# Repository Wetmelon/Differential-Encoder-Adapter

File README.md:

# Differential Encoder Adapter

This project is dedicated to a simple adapter board designed to convert 5V line driver encoders to single-ended encoders for use with the ODrive 3.x servo driver.

[Order Boards Here](https://oshpark.com/shared_projects/JfDf458t)

[BOM on Octopart available here](https://octopart.com/bom-tool/bUMGyQwH)

MIT License

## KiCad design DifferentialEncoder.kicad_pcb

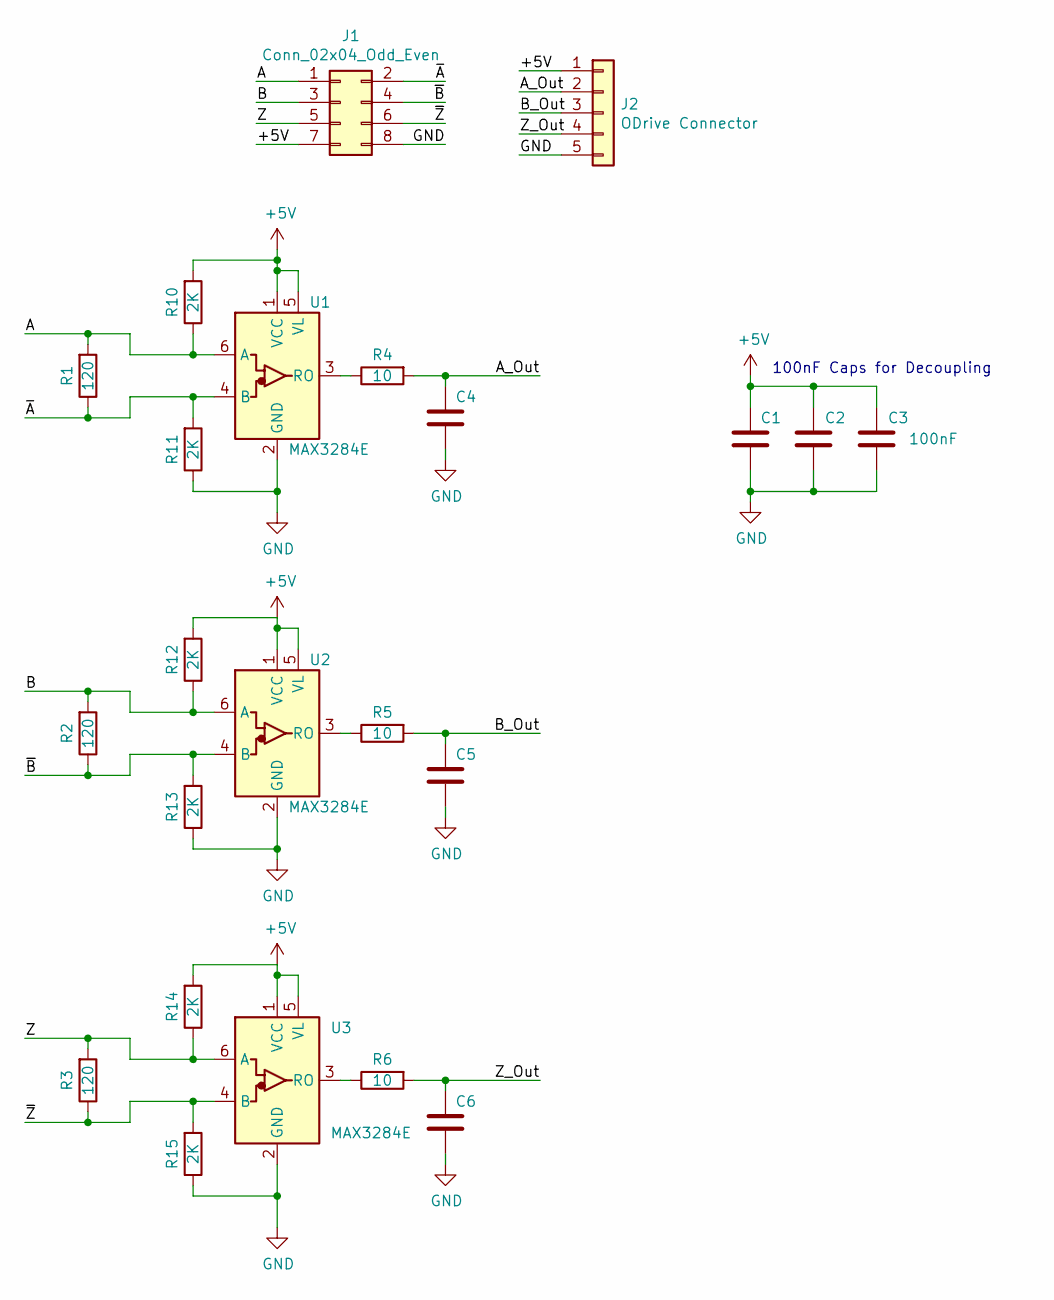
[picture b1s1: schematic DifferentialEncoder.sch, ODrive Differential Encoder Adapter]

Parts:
C1, C2, C3: 100nF; C_0805_2012Metric
C4, C5, C6: 1nF; C_0805_2012Metric
J1: Conn_02x04_Odd_Even; PinHeader_2x04_P2.54mm_Vertical
J2: ODrive Connector; PinHeader_1x05_P2.54mm_Vertical
R1, R2, R3: 120; R_0805_2012Metric_Pad1.15x1.40mm_HandSolder
R4, R5, R6: 10; R_0805_2012Metric_Pad1.15x1.40mm_HandSolder
R10, R11, R12, R13, R14, R15: 2K; R_0805_2012Metric_Pad1.15x1.40mm_HandSolder
U1, U2, U3: MAX3284E; SOT-23-6

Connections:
+5V: C1.1, C2.1, C3.1, J1.7, J2.1, R10.2, R12.2, R14.2, U1.1 (VCC), U1.5 (VL), U2.1 (VCC), U2.5 (VL), U3.1 (VCC), U3.5 (VL)
/A: J1.1, R1.2, R10.1, U1.6 (A)
/A_Out: C4.1, J2.2, R4.2
/B: J1.3, R2.2, R12.1, U2.6 (A)
/B_Out: C5.1, J2.3, R5.2
/Z: J1.5, R3.2, R14.1, U3.6 (A)
/Z_Out: C6.1, J2.4, R6.2
/~A: J1.2, R1.1, R11.2, U1.4 (B)
/~B: J1.4, R2.1, R13.2, U2.4 (B)
/~Z: J1.6, R3.1, R15.2, U3.4 (B)
GND: C1.2, C2.2, C3.2, C4.2, C5.2, C6.2, J1.8, J2.5, R11.1, R13.1, R15.1, U1.2 (GND), U2.2 (GND), U3.2 (GND)
unnamed: R4.1, U1.3 (RO)
unnamed: R5.1, U2.3 (RO)
unnamed: R6.1, U3.3 (RO)

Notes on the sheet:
100nF Caps for Decoupling

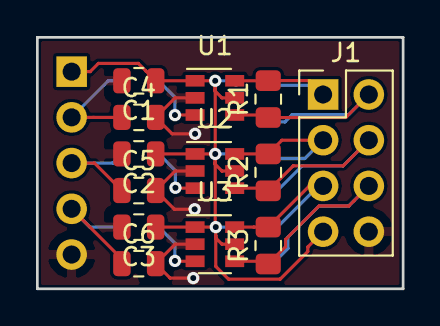
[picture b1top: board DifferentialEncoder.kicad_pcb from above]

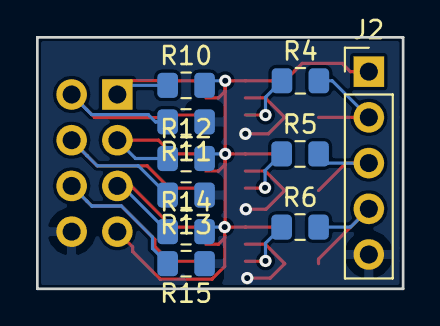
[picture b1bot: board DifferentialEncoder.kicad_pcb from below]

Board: 2 copper layers, 20.3 x 14.0 mm, 23 parts (10 on the bottom side), 14 nets.

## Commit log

2018-08-16 Create Revision 1
2018-08-19 Change some silkscreen, flip single-ended pins to back side
2019-05-28 Update differential adapter with termination etc.
